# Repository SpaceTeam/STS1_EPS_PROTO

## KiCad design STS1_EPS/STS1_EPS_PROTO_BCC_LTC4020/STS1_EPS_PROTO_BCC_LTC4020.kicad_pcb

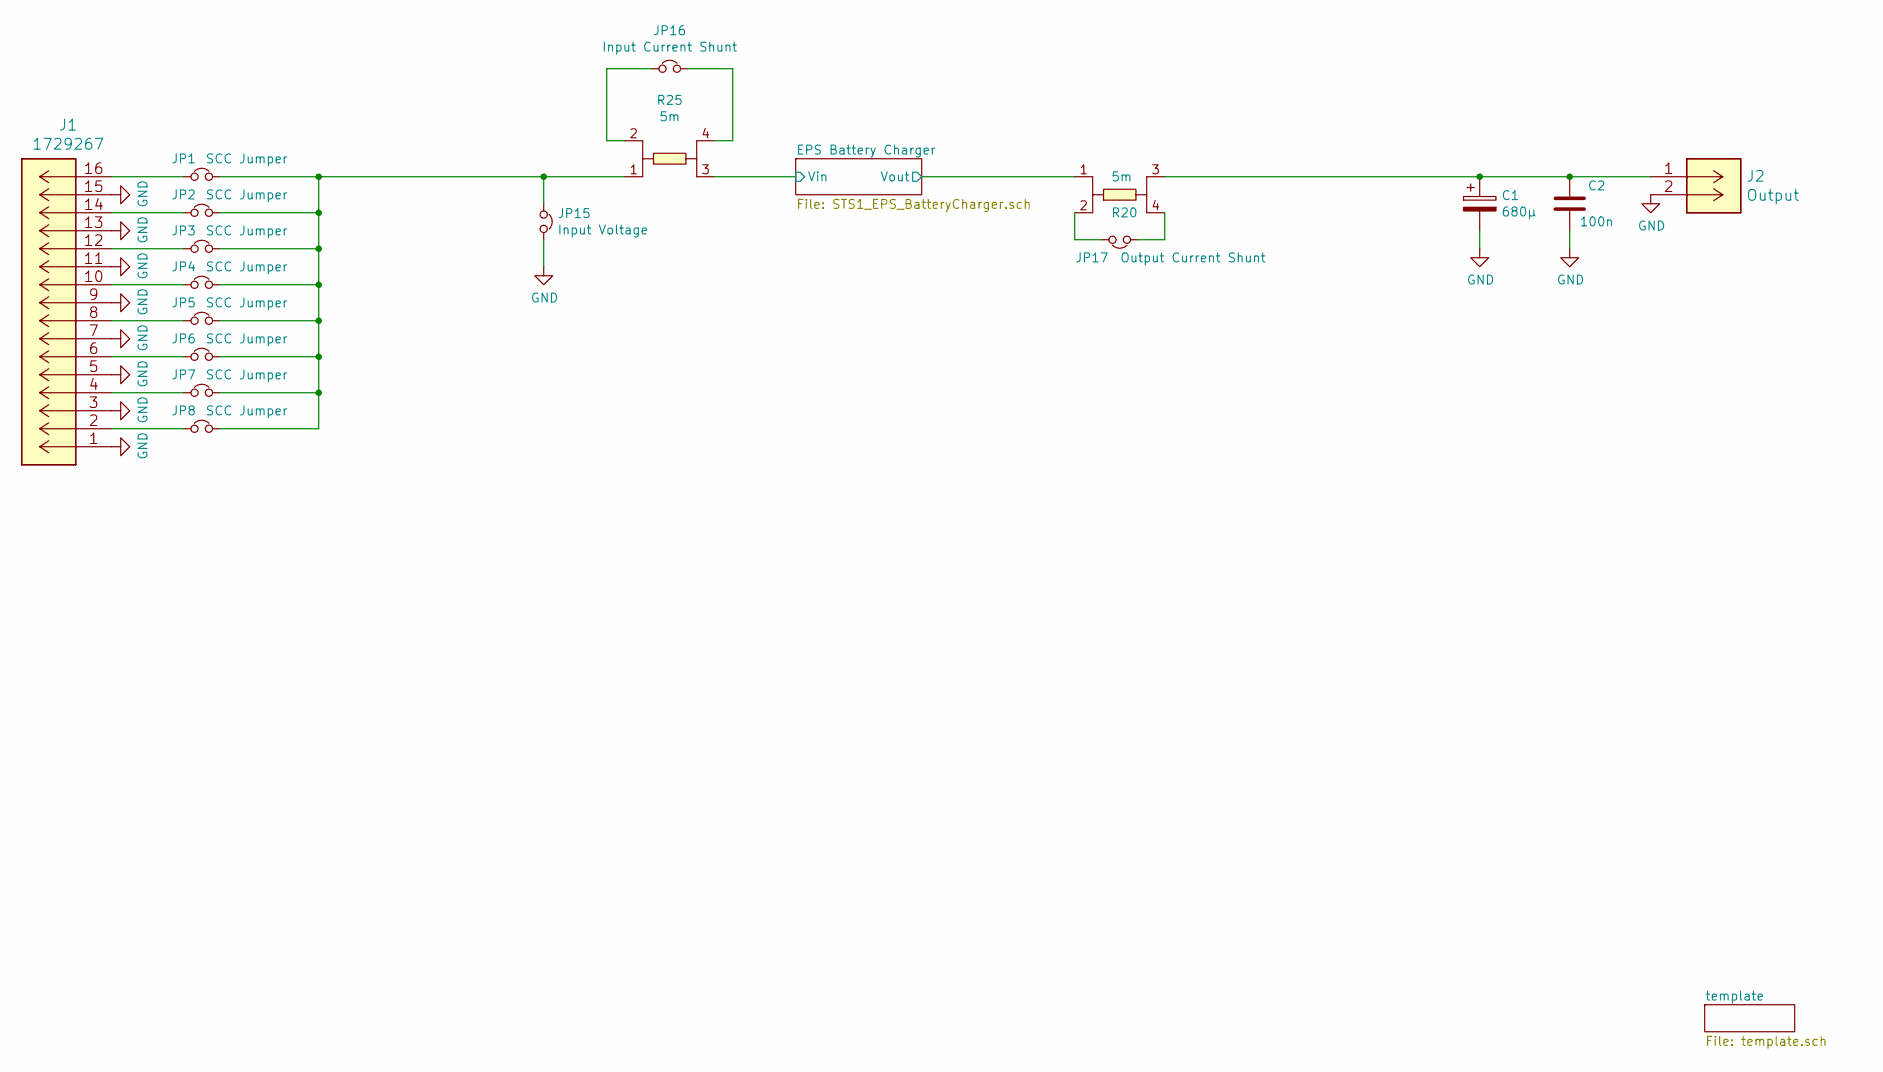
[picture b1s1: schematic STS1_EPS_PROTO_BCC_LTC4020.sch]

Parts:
C1: 680µ; CP_EIA-7361-438_AVX-U
C2: 100n; C_0805_2012Metric
J1: 1729267; 1984756
J2: Output; 1888807
JP1, JP2, JP3, JP4, JP5, JP6, JP7, JP8: SCC Jumper; PinHeader_1x02_P2.54mm_Vertical
JP15: Input Voltage; PinHeader_1x02_P2.54mm_Vertical
JP16: Input Current Shunt; PinHeader_1x02_P2.54mm_Vertical
JP17: Output Current Shunt; PinHeader_1x02_P2.54mm_Vertical
R20, R25: 5m; CST0612-FC-R002E

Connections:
/EPS Battery Charger/Vin: R25.3; also elsewhere on the board
/EPS Battery Charger/Vout: R20.1; also elsewhere on the board
GND: C1.2, C2.1, J1.1, J1.3, J1.5, J1.7, J1.9, J1.11, J1.13, J1.15, J2.2, JP15.2; also elsewhere on the board
unnamed: C1.1, C2.2, J2.1, R20.3
unnamed: J1.2, JP8.1
unnamed: J1.4, JP7.1
unnamed: J1.6, JP6.1
unnamed: J1.8, JP5.1
unnamed: J1.10, JP4.1
unnamed: J1.12, JP3.1
unnamed: J1.14, JP2.1
unnamed: J1.16, JP1.1
unnamed: JP1.2, JP2.2, JP3.2, JP4.2, JP5.2, JP6.2, JP7.2, JP8.2, JP15.1, R25.1
unnamed: JP16.1, R25.2
unnamed: JP16.2, R25.4
unnamed: JP17.1, R20.4
unnamed: JP17.2, R20.2

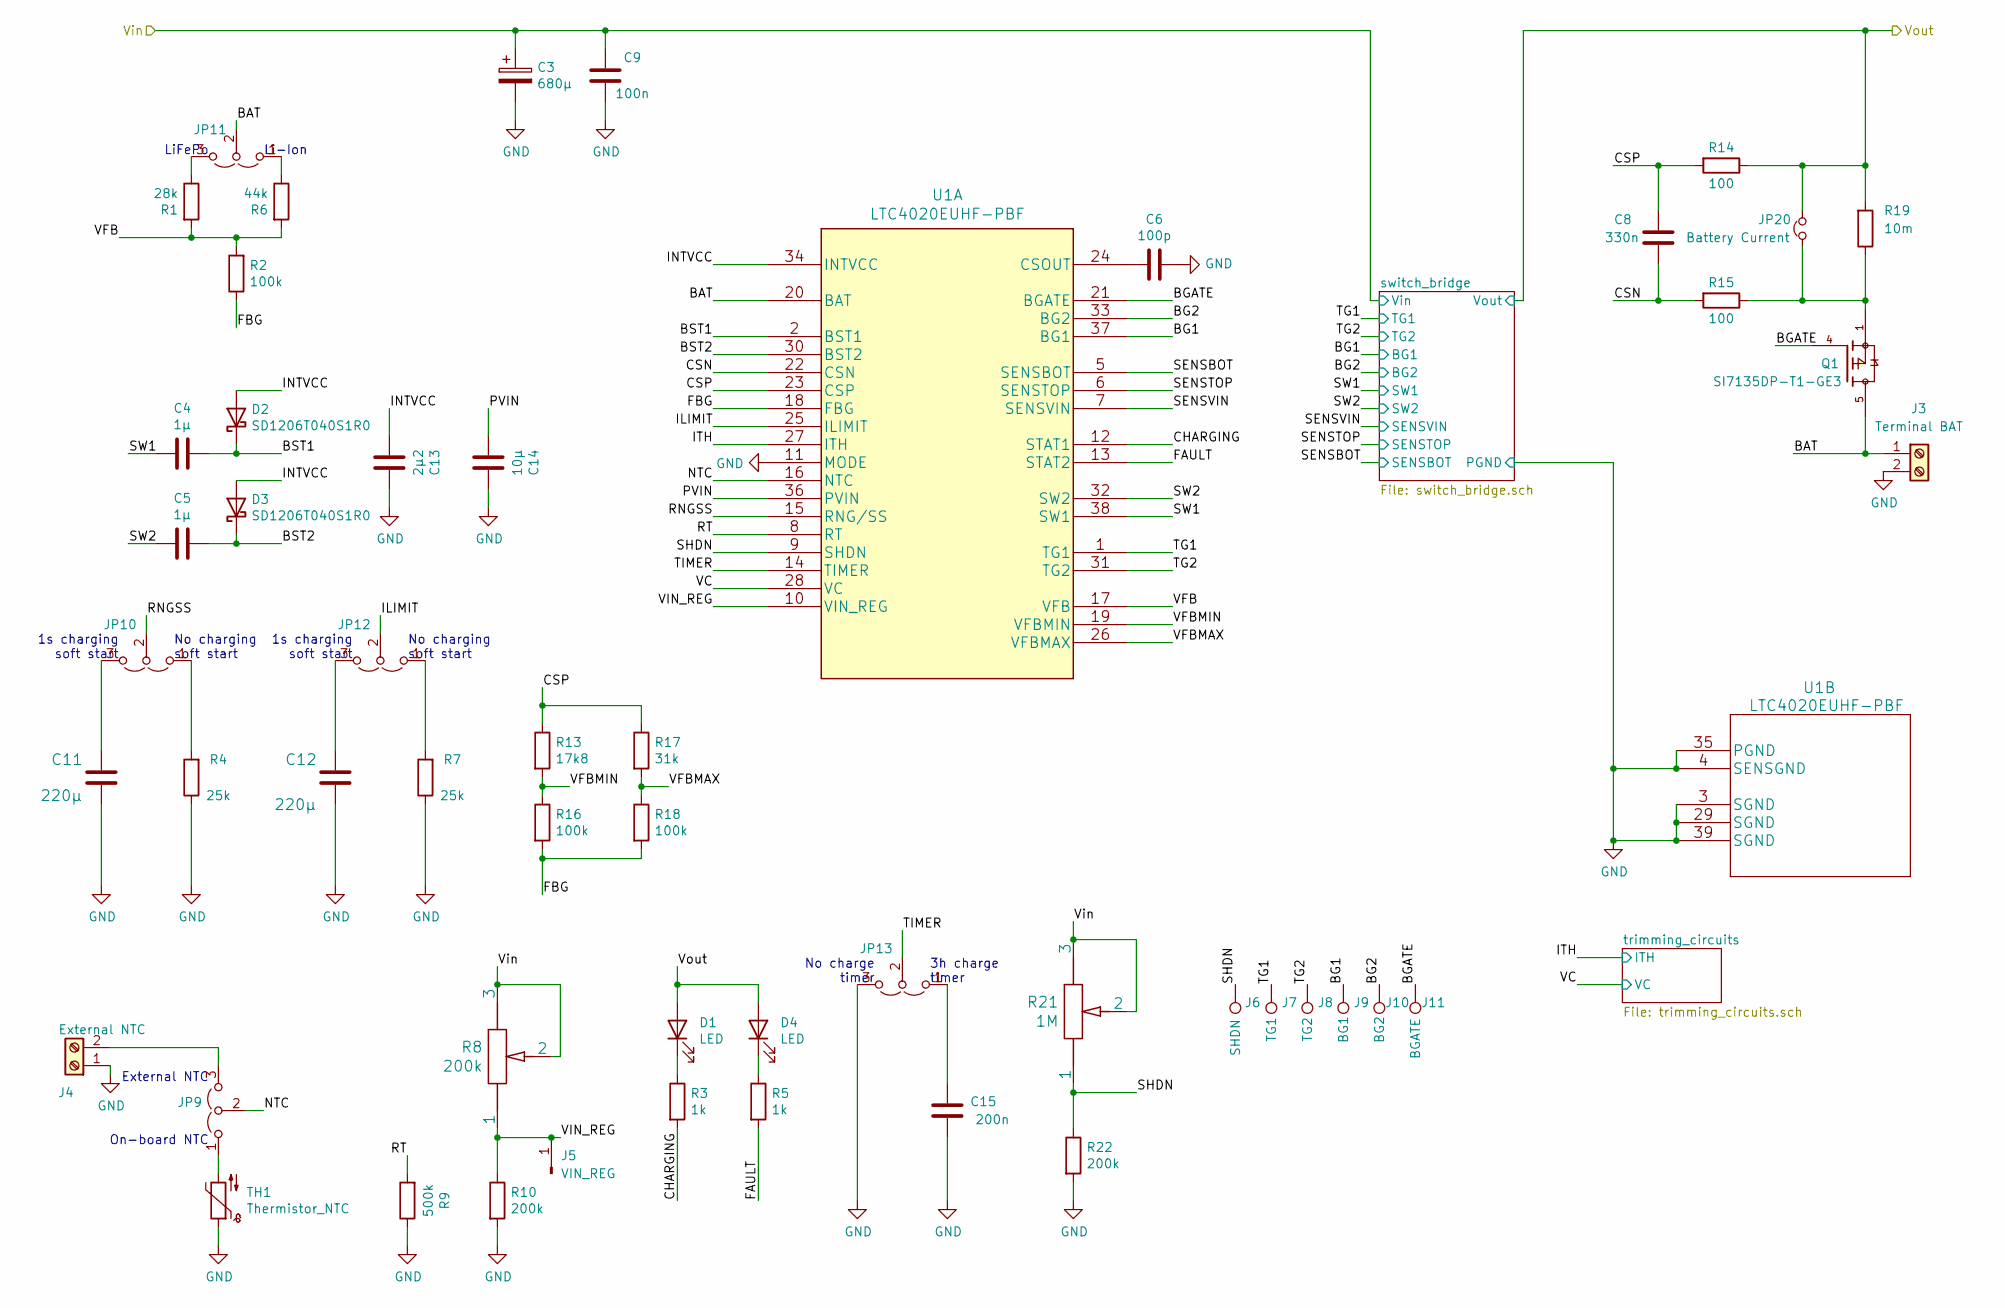
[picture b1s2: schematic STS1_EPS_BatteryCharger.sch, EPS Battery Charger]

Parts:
C3: 680µ; CP_EIA-7361-438_AVX-U
C4, C5: 1µ; C_0805_2012Metric
C6: 100p; C_0805_2012Metric
C8: 330n; C_0805_2012Metric
C9: 100n; C_0805_2012Metric
C11, C12: 220µ; CP_EIA-3528-12_Kemet-T
C13: 2µ2; C_0805_2012Metric
C14: 10µ; C_0805_2012Metric
C15: 200n; C_0805_2012Metric
D1, D4: LED; LED_0805_2012Metric
D2, D3: SD1206T040S1R0; D_1206_3216Metric
J3: Terminal BAT; 1725656
J4: External NTC; 1725656
J5: VIN_REG; PinHeader_1x01_P2.54mm_Vertical
J6: SHDN; PinHeader_1x01_P2.54mm_Vertical
J7: TG1; PinHeader_1x01_P2.54mm_Vertical
J8: TG2; PinHeader_1x01_P2.54mm_Vertical
J9: BG1; PinHeader_1x01_P2.54mm_Vertical
J10: BG2; PinHeader_1x01_P2.54mm_Vertical
J11: BGATE; PinHeader_1x01_P2.54mm_Vertical
JP9, JP10, JP11, JP12, JP13: Jumper_3_Open; PinHeader_1x03_P2.54mm_Vertical
JP20: Battery Current; PinHeader_1x02_P2.54mm_Vertical
Q1: SI7135DP-T1-GE3; TRANS_SI7135DP-T1-GE3; PARTREV A
R1: 28k; R_0805_2012Metric
R2, R16, R18: 100k; R_0805_2012Metric
R3, R5: 1k; R_0805_2012Metric
R4, R7: 25k; R_0805_2012Metric
R6: 44k; R_0805_2012Metric
R8: 200k; TS53YL 20K 20&percent_
R9: 500k; R_0805_2012Metric
R10, R22: 200k; R_0805_2012Metric
R13: 17k8; R_0805_2012Metric
R14, R15: 100; R_0805_2012Metric
R17: 31k; R_0805_2012Metric
R19: 10m; R_1206_3216Metric; Part Nr. PCS1206DR0100ET
R21: 1M; TS53YL 20K 20&percent_
TH1: Thermistor_NTC; R_0603_1608Metric
U1: LTC4020EUHF-PBF

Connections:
/EPS Battery Charger/BAT: J3.1, JP11.2 (C), Q1.5, U1.20 (BAT)
/EPS Battery Charger/BG1: J9.1, U1.37 (BG1); also elsewhere on the board
/EPS Battery Charger/BG2: J10.1, U1.33 (BG2); also elsewhere on the board
/EPS Battery Charger/BGATE: J11.1, Q1.4, U1.21 (BGATE)
/EPS Battery Charger/BST1: C4.1, D2.1 (K), U1.2 (BST1)
/EPS Battery Charger/BST2: C5.1, D3.1 (K), U1.30 (BST2)
/EPS Battery Charger/CHARGING: R3.2, U1.12 (STAT1)
/EPS Battery Charger/CSN: C8.2, R15.2, U1.22 (CSN)
/EPS Battery Charger/CSP: C8.1, R13.1, R14.2, R17.1, U1.23 (CSP)
/EPS Battery Charger/FAULT: R5.2, U1.13 (STAT2)
/EPS Battery Charger/FBG: R2.1, R16.2, R18.2, U1.18 (FBG)
/EPS Battery Charger/ILIMIT: JP12.2 (C), U1.25 (ILIMIT)
/EPS Battery Charger/INTVCC: C13.2, D2.2 (A), D3.2 (A), U1.34 (INTVCC)
/EPS Battery Charger/ITH: U1.27 (ITH); also elsewhere on the board
/EPS Battery Charger/NTC: JP9.2 (C), U1.16 (NTC)
/EPS Battery Charger/PVIN: C14.2, U1.36 (PVIN)
/EPS Battery Charger/RNGSS: JP10.2 (C), U1.15 (RNG/SS)
/EPS Battery Charger/RT: R9.2, U1.8 (RT)
/EPS Battery Charger/SENSBOT: U1.5 (SENSBOT); also elsewhere on the board
/EPS Battery Charger/SENSTOP: U1.6 (SENSTOP); also elsewhere on the board
/EPS Battery Charger/SENSVIN: U1.7 (SENSVIN); also elsewhere on the board
/EPS Battery Charger/SHDN: J6.1, R21.1, R22.1, U1.9 (SHDN)
/EPS Battery Charger/SW1: C4.2, U1.38 (SW1); also elsewhere on the board
/EPS Battery Charger/SW2: C5.2, U1.32 (SW2); also elsewhere on the board
/EPS Battery Charger/TG1: J7.1, U1.1 (TG1); also elsewhere on the board
/EPS Battery Charger/TG2: J8.1, U1.31 (TG2); also elsewhere on the board
/EPS Battery Charger/TIMER: JP13.2 (C), U1.14 (TIMER)
/EPS Battery Charger/VC: U1.28 (VC); also elsewhere on the board
/EPS Battery Charger/VFB: R1.2, R2.2, R6.2, U1.17 (VFB)
/EPS Battery Charger/VFBMAX: R17.2, R18.1, U1.26 (VFBMAX)
/EPS Battery Charger/VFBMIN: R13.2, R16.1, U1.19 (VFBMIN)
/EPS Battery Charger/VIN_REG: J5.1, R8.1, R10.1, U1.10 (VIN_REG)
/EPS Battery Charger/Vin: C3.1, C9.2, R8.2, R8.3, R21.2, R21.3; also elsewhere on the board
/EPS Battery Charger/Vout: D1.2 (A), D4.2 (A), JP20.2, R14.1, R19.2; also elsewhere on the board
GND: C3.2, C6.1, C9.1, C11.1, C12.1, C13.1, C14.1, C15.2, J3.2, J4.1, JP13.3 (B), R4.1, R7.1, R9.1, R10.2, R22.2, TH1.1, U1.3 (SGND), U1.4 (SENSGND), U1.11 (MODE), U1.29 (SGND), U1.35 (PGND), U1.39 (SGND); also elsewhere on the board
unnamed: C6.2, U1.24 (CSOUT)
unnamed: C11.2, JP10.3 (B)
unnamed: C12.2, JP12.3 (B)
unnamed: C15.1, JP13.1 (A)
unnamed: D1.1 (K), R3.1
unnamed: D4.1 (K), R5.1
unnamed: J4.2, JP9.3 (B)
unnamed: JP9.1 (A), TH1.2
unnamed: JP10.1 (A), R4.2
unnamed: JP11.1 (A), R6.1
unnamed: JP11.3 (B), R1.1
unnamed: JP12.1 (A), R7.2
unnamed: JP20.1, Q1.1, R15.1, R19.1

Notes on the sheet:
LiFePo
Li-Ion
No charge timer
3h charge timer
External NTC
On-board NTC
No charging soft start
1s charging soft start

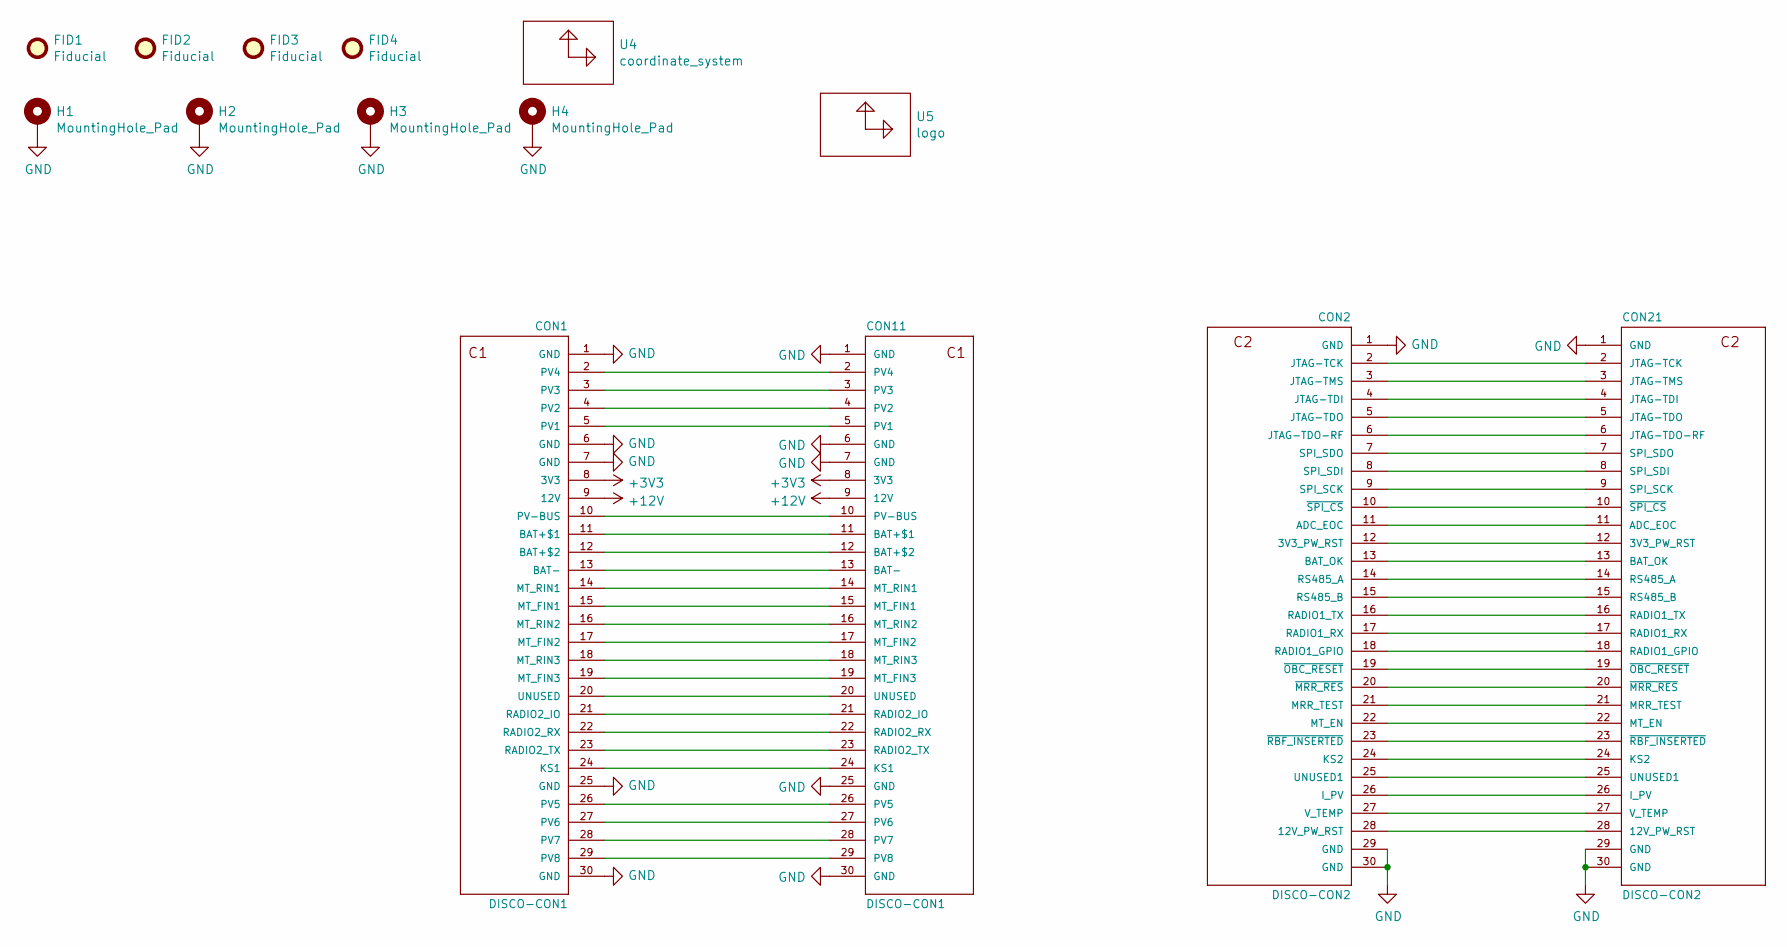
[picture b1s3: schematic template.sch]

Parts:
CON1, CON11: DISCO-CON1; Cubesatconnector
CON2, CON21: DISCO-CON2; Cubesatconnector
FID1, FID2, FID3, FID4: Fiducial; Fiducial_0.75mm_Mask1.5mm
H1, H2, H3, H4: MountingHole_Pad; MountingHole_3.2mm_M3_Pad_Via
U4: coordinate_system; Coordinates
U5: logo; STLogoTiny

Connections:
+3V3: CON1.8 (3V3), CON11.8 (3V3)
+12V: CON1.9 (12V), CON11.9 (12V)
GND: CON1.1 (GND), CON1.6 (GND), CON1.7 (GND), CON1.25 (GND), CON1.30 (GND), CON2.1 (GND), CON2.29 (GND), CON2.30 (GND), CON11.1 (GND), CON11.6 (GND), CON11.7 (GND), CON11.25 (GND), CON11.30 (GND), CON21.1 (GND), CON21.29 (GND), CON21.30 (GND), H1.1, H2.1, H3.1, H4.1; also elsewhere on the board
unnamed: CON1.2 (PV4), CON11.2 (PV4)
unnamed: CON1.3 (PV3), CON11.3 (PV3)
unnamed: CON1.4 (PV2), CON11.4 (PV2)
unnamed: CON1.5 (PV1), CON11.5 (PV1)
unnamed: CON1.10 (PV-BUS), CON11.10 (PV-BUS)
unnamed: CON1.11 (BAT+$1), CON11.11 (BAT+$1)
unnamed: CON1.12 (BAT+$2), CON11.12 (BAT+$2)
unnamed: CON1.13 (BAT-), CON11.13 (BAT-)
unnamed: CON1.14 (MT_RIN1), CON11.14 (MT_RIN1)
unnamed: CON1.15 (MT_FIN1), CON11.15 (MT_FIN1)
unnamed: CON1.16 (MT_RIN2), CON11.16 (MT_RIN2)
unnamed: CON1.17 (MT_FIN2), CON11.17 (MT_FIN2)
unnamed: CON1.18 (MT_RIN3), CON11.18 (MT_RIN3)
unnamed: CON1.19 (MT_FIN3), CON11.19 (MT_FIN3)
unnamed: CON1.20 (UNUSED), CON11.20 (UNUSED)
unnamed: CON1.21 (RADIO2_IO), CON11.21 (RADIO2_IO)
unnamed: CON1.22 (RADIO2_RX), CON11.22 (RADIO2_RX)
unnamed: CON1.23 (RADIO2_TX), CON11.23 (RADIO2_TX)
unnamed: CON1.24 (KS1), CON11.24 (KS1)
unnamed: CON1.26 (PV5), CON11.26 (PV5)
unnamed: CON1.27 (PV6), CON11.27 (PV6)
unnamed: CON1.28 (PV7), CON11.28 (PV7)
unnamed: CON1.29 (PV8), CON11.29 (PV8)
unnamed: CON2.2 (JTAG-TCK), CON21.2 (JTAG-TCK)
unnamed: CON2.3 (JTAG-TMS), CON21.3 (JTAG-TMS)
unnamed: CON2.4 (JTAG-TDI), CON21.4 (JTAG-TDI)
unnamed: CON2.5 (JTAG-TDO), CON21.5 (JTAG-TDO)
unnamed: CON2.6 (JTAG-TDO-RF), CON21.6 (JTAG-TDO-RF)
unnamed: CON2.7 (SPI_SDO), CON21.7 (SPI_SDO)
unnamed: CON2.8 (SPI_SDI), CON21.8 (SPI_SDI)
unnamed: CON2.9 (SPI_SCK), CON21.9 (SPI_SCK)
unnamed: CON2.10 (~SPI_CS), CON21.10 (~SPI_CS)
unnamed: CON2.11 (ADC_EOC), CON21.11 (ADC_EOC)
unnamed: CON2.12 (3V3_PW_RST), CON21.12 (3V3_PW_RST)
unnamed: CON2.13 (BAT_OK), CON21.13 (BAT_OK)
unnamed: CON2.14 (RS485_A), CON21.14 (RS485_A)
unnamed: CON2.15 (RS485_B), CON21.15 (RS485_B)
unnamed: CON2.16 (RADIO1_TX), CON21.16 (RADIO1_TX)
unnamed: CON2.17 (RADIO1_RX), CON21.17 (RADIO1_RX)
unnamed: CON2.18 (RADIO1_GPIO), CON21.18 (RADIO1_GPIO)
unnamed: CON2.19 (~OBC_RESET), CON21.19 (~OBC_RESET)
unnamed: CON2.20 (~MRR_RES), CON21.20 (~MRR_RES)
unnamed: CON2.21 (MRR_TEST), CON21.21 (MRR_TEST)
unnamed: CON2.22 (MT_EN), CON21.22 (MT_EN)
unnamed: CON2.23 (~RBF_INSERTED), CON21.23 (~RBF_INSERTED)
unnamed: CON2.24 (KS2), CON21.24 (KS2)
unnamed: CON2.25 (UNUSED1), CON21.25 (UNUSED1)
unnamed: CON2.26 (I_PV), CON21.26 (I_PV)
unnamed: CON2.27 (V_TEMP), CON21.27 (V_TEMP)
unnamed: CON2.28 (12V_PW_RST), CON21.28 (12V_PW_RST)

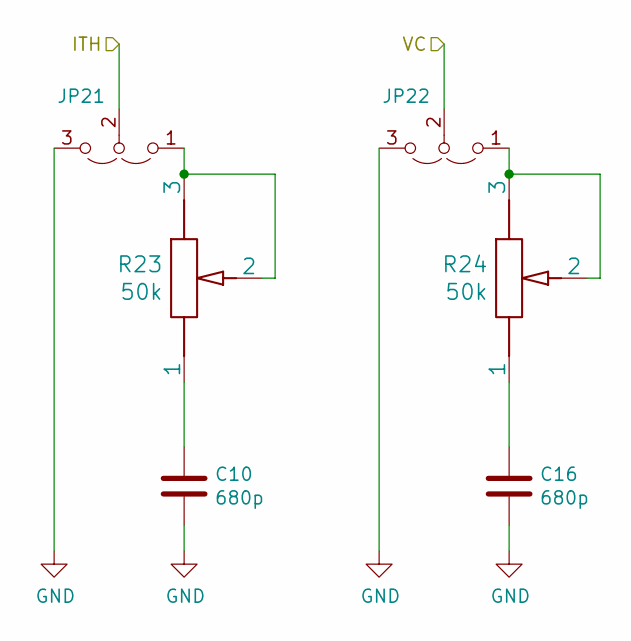
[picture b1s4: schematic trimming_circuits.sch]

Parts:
C10, C16: 680p; C_0805_2012Metric
JP21, JP22: Jumper_3_Open; PinHeader_1x03_P2.54mm_Vertical
R23, R24: 50k; TS53YL 20K 20&percent_

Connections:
/EPS Battery Charger/ITH: JP21.2 (C); also elsewhere on the board
/EPS Battery Charger/VC: JP22.2 (C); also elsewhere on the board
GND: C10.2, C16.2, JP21.3 (B), JP22.3 (B); also elsewhere on the board
unnamed: C10.1, R23.1
unnamed: C16.1, R24.1
unnamed: JP21.1 (A), R23.2, R23.3
unnamed: JP22.1 (A), R24.2, R24.3

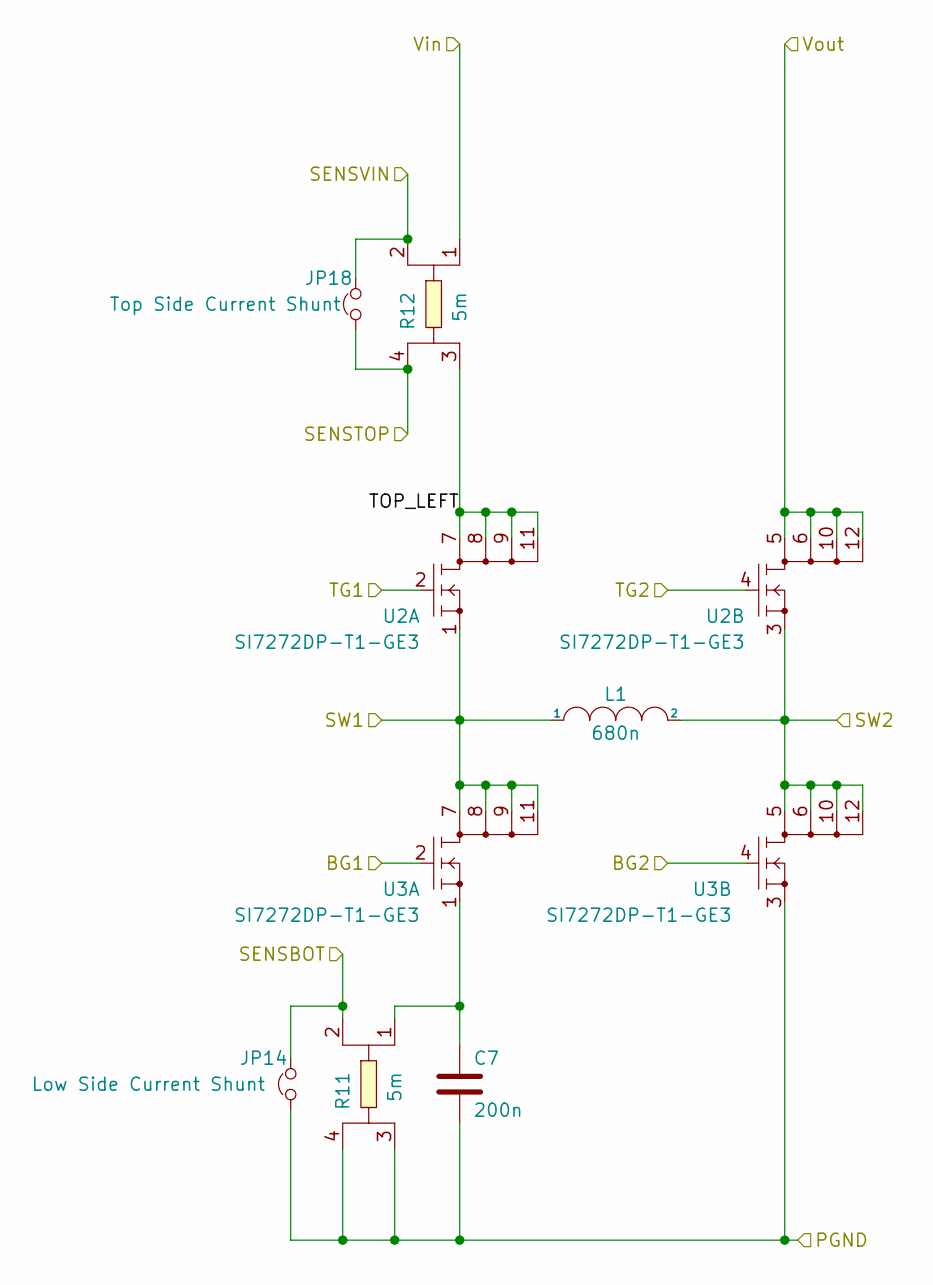
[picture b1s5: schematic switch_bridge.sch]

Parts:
C7: 200n; C_1812_4532Metric
JP14: Low Side Current Shunt; PinHeader_1x02_P2.54mm_Vertical
JP18: Top Side Current Shunt; PinHeader_1x02_P2.54mm_Vertical
L1: 680n; INDPM7366X500N
R11, R12: 5m; CST0612-FC-R002E
U2, U3: SI7272DP-T1-GE3; SI7288DPT1GE3

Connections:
/EPS Battery Charger/BG1: U3.2 (G1); also elsewhere on the board
/EPS Battery Charger/BG2: U3.4 (G2); also elsewhere on the board
/EPS Battery Charger/SENSBOT: JP14.2, R11.2; also elsewhere on the board
/EPS Battery Charger/SENSTOP: JP18.1, R12.4; also elsewhere on the board
/EPS Battery Charger/SENSVIN: JP18.2, R12.2; also elsewhere on the board
/EPS Battery Charger/SW1: L1.1, U2.1 (S1), U3.7 (D1_1), U3.8 (D1_2), U3.9 (D1_3), U3.11 (D1_4); also elsewhere on the board
/EPS Battery Charger/SW2: L1.2, U2.3 (S2), U3.5 (D2_1), U3.6 (D2_2), U3.10 (D2_3), U3.12 (D2_4); also elsewhere on the board
/EPS Battery Charger/TG1: U2.2 (G1); also elsewhere on the board
/EPS Battery Charger/TG2: U2.4 (G2); also elsewhere on the board
/EPS Battery Charger/Vin: R12.1; also elsewhere on the board
/EPS Battery Charger/Vout: U2.5 (D2_1), U2.6 (D2_2), U2.10 (D2_3), U2.12 (D2_4); also elsewhere on the board
/EPS Battery Charger/switch_bridge/TOP_LEFT: R12.3, U2.7 (D1_1), U2.8 (D1_2), U2.9 (D1_3), U2.11 (D1_4)
GND: C7.1, JP14.1, R11.3, R11.4, U3.3 (S2); also elsewhere on the board
unnamed: C7.2, R11.1, U3.1 (S1)

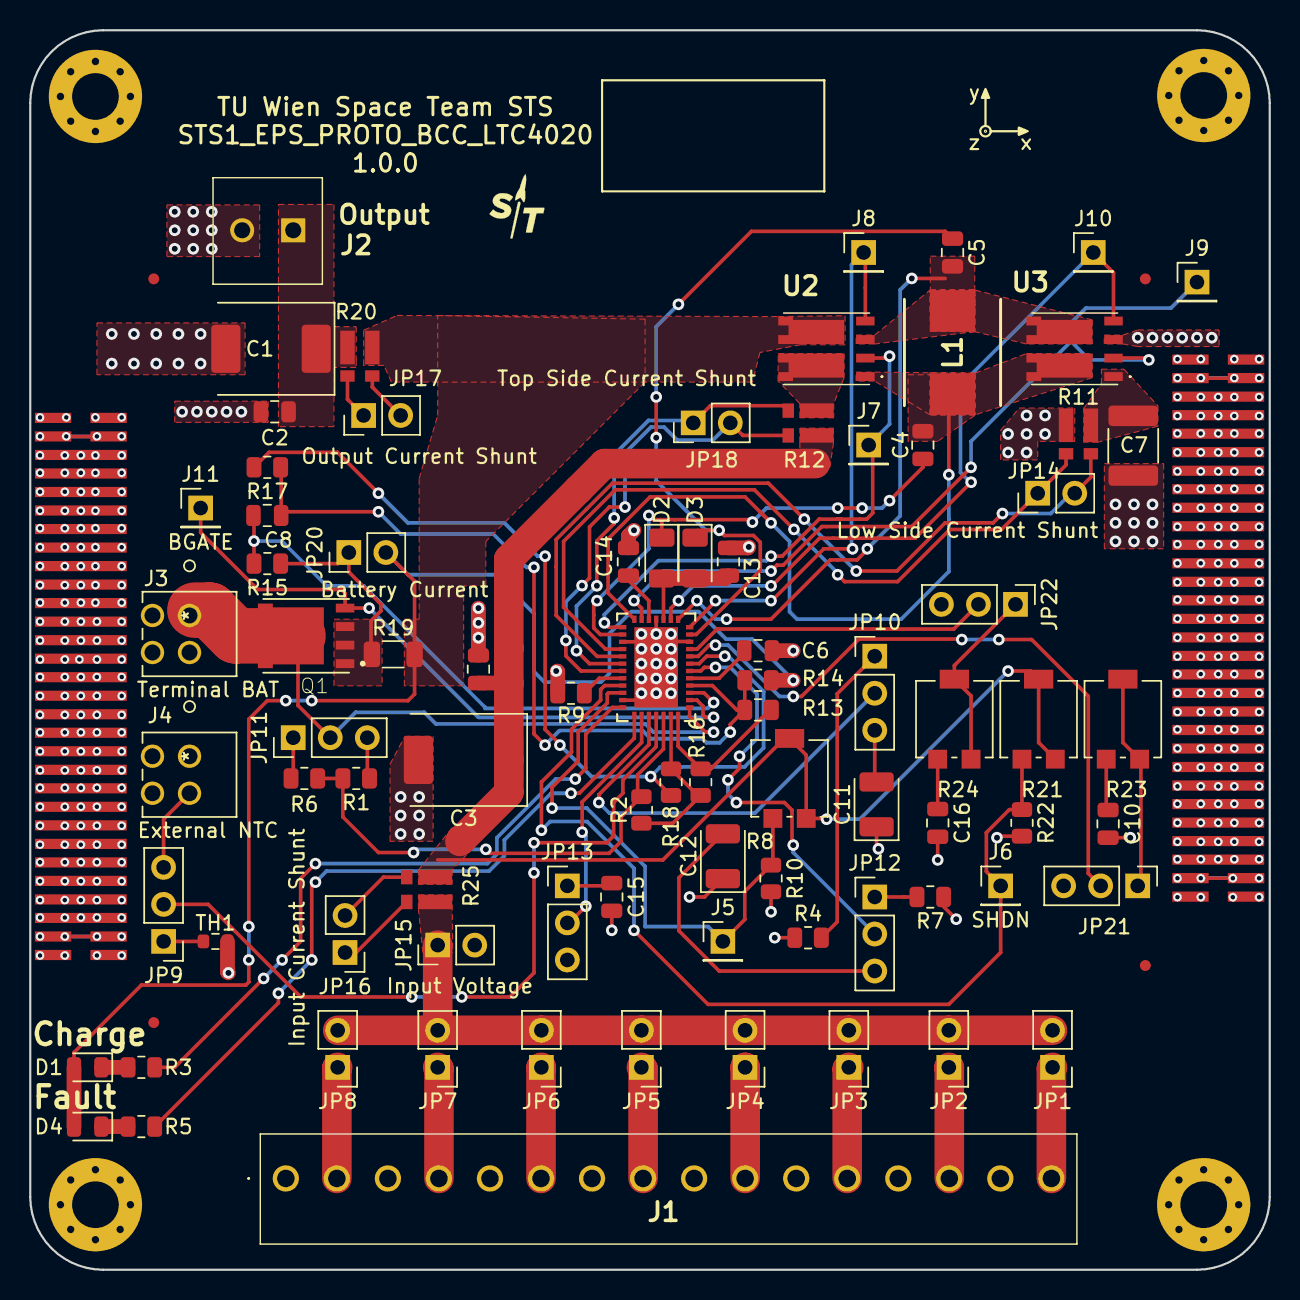
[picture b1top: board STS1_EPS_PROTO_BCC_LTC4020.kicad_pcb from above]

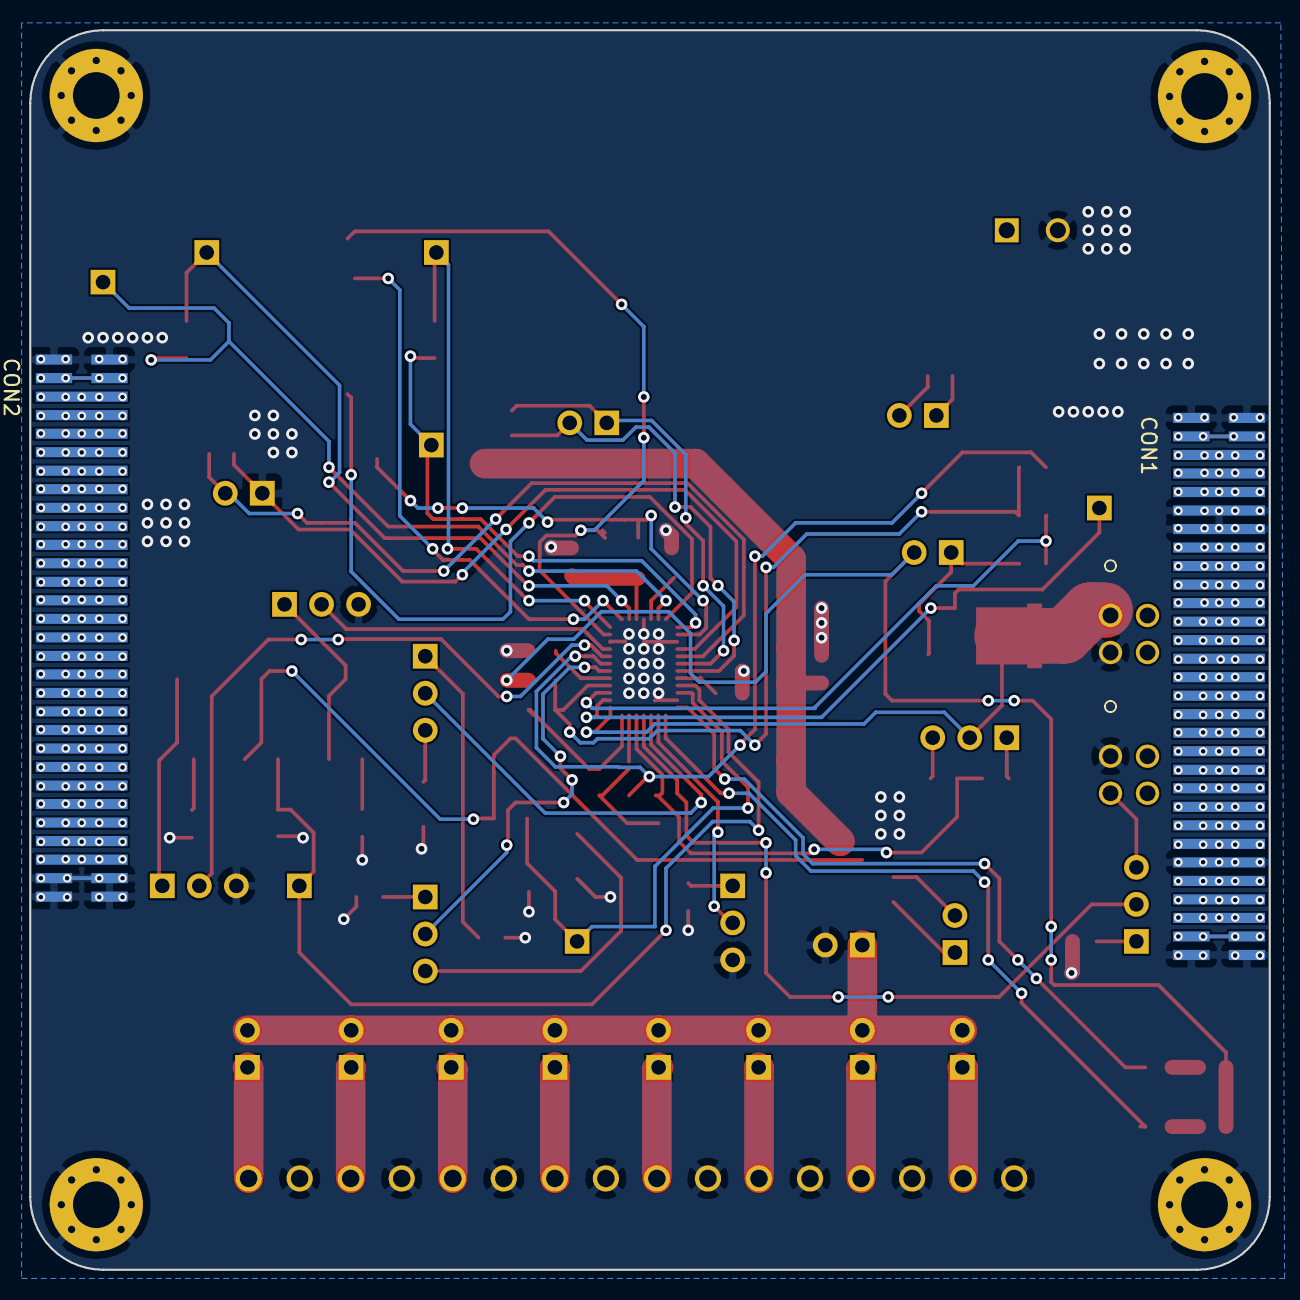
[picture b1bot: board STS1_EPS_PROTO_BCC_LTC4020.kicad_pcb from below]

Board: 2 copper layers, 85.0 x 85.0 mm, 97 parts (2 on the bottom side), 120 nets.

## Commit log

2021-06-25 Solar cell controller based on L6920d ready for reaview.
2021-06-27 Created project for LTC4020 Battery Charger prototype board.
2021-06-27 Added some missing KiCad library files.
2021-06-27 Library paths of STS_EPS_PROTO_SCC_L6920 project are now relative.
2021-06-27 Libraries should work again.
2021-06-27 Fixed library paths for STS1_EPS_PROTO_BCC_LTC4020 project.
2021-06-27 Re-added battery charger schematic for STS1_EPS_PROTO_BCC_LTC4020 project.
2021-06-28 Worked on STS1_EPS_PROTO_BCC_LTC4020 pcb.
2021-07-02 Reworked BCC
2021-07-04 - STS1_EPS_PROTO_SCC_L6920 now uses the STS1 PCB template and is again ready for review. - WOrked on STS1_EPS_PROTO_BCC_LTC4020.
2021-07-12 Intermediate state.
2021-07-15 BCC ready for review
2021-08-08 Incorporated feedback into BCC and SCC - Fixed "unspecified" pin type warnings - Added correct test point symbols - Added thermal blockers - Added DRC parameters and fixed DRC issues - Adapted CubeSa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
2021-08-09 Replaced electrolyte capacitors of SCC with tantalum capacitors.
2021-08-09 Changed footprints of some components.
2021-08-27 Part references of U2 and U3 were intersecting with their solder pads. Fixed that.

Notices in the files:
parts and their libraries:
Copyright 2016 Accelerated Designs. All rights reserved.
Copyright 2021 Accelerated Designs. All rights reserved.
